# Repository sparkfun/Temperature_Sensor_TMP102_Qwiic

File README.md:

SparkFun Digital Temperature Sensor - TMP102 (Qwiic)
============================================

[  
*SparkFun Digital Temperature Sensor - TMP102 (Qwiic) (SEN-16304)*](https://www.sparkfun.com/products/16304)

Qwiic enabled breakout board for TMP102 digital temperature sensor [The datasheet can be found here.](https://www.sparkfun.com/datasheets/Sensors/Temperature/tmp102.pdf)

This board was created in Eagle v6.4.0. 

Repository Contents
-------------------

* **/Documentation** - Datasheet for the TMP102 (.pdf)
* **/Hardware** - All Eagle design files (.brd and .sch)
* **/Production** - Production panel files

Documentation
--------------
* **[Library](https://github.com/sparkfun/SparkFun_TMP102_Arduino_Library)** - Arduino library for the SparkFun Digital Temperature Sensor - TMP102 (Qwiic).
* **[Hookup Guide](https://learn.sparkfun.com/tutorials/sparkfun-qwiic-digital-temperature-sensor---tmp102-hookup-guide)** - Basic hookup guide for the SparkFun Digital Temperature Sensor - TMP102 (Qwiic).
  
License Information
-------------------
The hardware is released under [Creative Commons Share-alike 3.0](http://creativecommons.org/licenses/by-sa/3.0/).  
All other code is open source so please feel free to do anything you want with it; you buy me a beer if you use this and we meet someday ([Beerware license](http://en.wikipedia.org/wiki/Beerware)).

Design by Kade Alexander Jensen

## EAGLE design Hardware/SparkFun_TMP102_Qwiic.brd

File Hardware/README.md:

SparkFun Temperature Sensor TMP102 (Qwiic) Design Files
=====================================

The .sch and .brd files hare are Eagle CAD schematic and PCB design files from SparkFun Electronics.
A freeware version of Eagle can be found [here](http://www.cadsoftusa.com/download-eagle/freeware/).

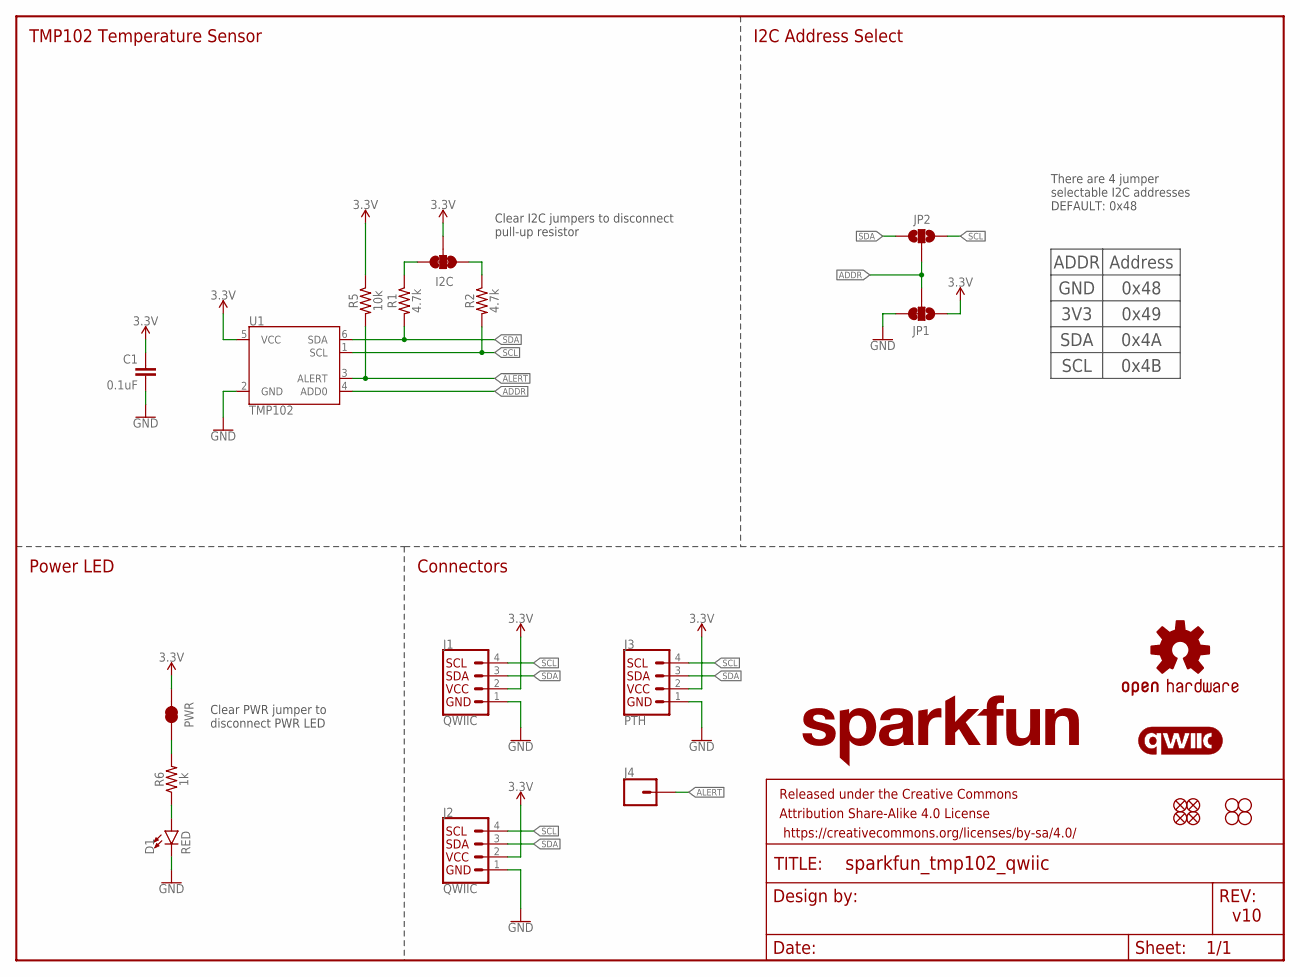
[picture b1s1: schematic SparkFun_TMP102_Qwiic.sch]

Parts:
C1: 0.1uF; 0603
D1: RED; LED-0603
FD1, FD2, FD3, FD4: FIDUCIALUFIDUCIAL; FIDUCIAL-MICRO
FRAME1: FRAME-LETTER; CREATIVE_COMMONS
H1, H2, H3, H4: STAND-OFF
J1, J2: QWIIC; JST04_1MM_RA
J3: PTH; 1X04_NO_SILK
J4: CONN_01PTH_NO_SILK_YES_STOP; 1X01_NO_SILK
JP1: JUMPER-SMT_3_1-NC_TRACE_NO-SILK; SMT-JUMPER_3_1-NC_TRACE_NO-SILK
JP2: JUMPER-SMT_3_NO_NO-SILK; SMT-JUMPER_3_NO_NO-SILK
JP3: I2C; SMT-JUMPER_3_2-NC_TRACE_SILK
JP4: PWR; SMT-JUMPER_2_NC_TRACE_SILK
LOGO1: SFE_LOGO_NAME.1_INCH; SFE_LOGO_NAME_.1
LOGO2: QWIIC_LOGO_5MM; QWIIC_5MM
LOGO3: OSHW-LOGOS; OSHW-LOGO-S
R1, R2: 4.7k; 0603
R5: 10k; 0603
R6: 1k; 0603
U1: TMP102; SOT563

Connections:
3.3V: C1.1, J1.2, J2.2, J3.2, JP1.1, JP3.2, JP4.2, R5.1, U1.5 (VCC)
!ALERT: J4.1, R5.2, U1.3 (ALERT)
ADDR: JP1.2, JP2.2, U1.4 (ADD0)
GND: C1.2, D1.C, J1.1, J2.1, J3.1, JP1.3, U1.2 (GND)
unnamed: JP3.3, R1.1
unnamed: JP3.1, R2.1
unnamed: D1.A, R6.1
unnamed: JP4.1, R6.2
SCL: J1.4, J2.4, J3.4, JP2.1, R2.2, U1.1 (SCL)
SDA: J1.3, J2.3, J3.3, JP2.3, R1.2, U1.6 (SDA)

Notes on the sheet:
v10
Address
0x48
0x49
0x4A
0x4B
GND
3V3
SDA
SCL
ADDR
I2C Address Select
TMP102 Temperature Sensor
Connectors
There are 4 jumper selectable I2C addresses DEFAULT: 0x48
Clear I2C jumpers to disconnect pull-up resistor
Clear PWR jumper to disconnect PWR LED
Power LED

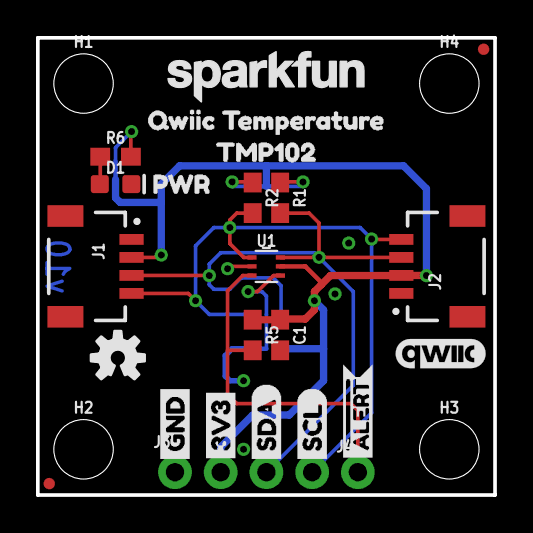
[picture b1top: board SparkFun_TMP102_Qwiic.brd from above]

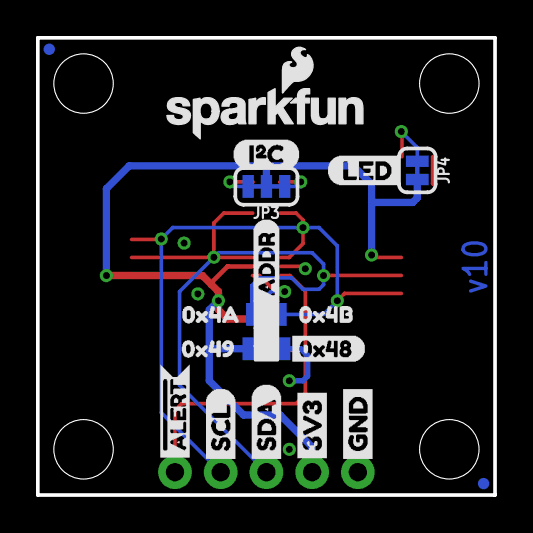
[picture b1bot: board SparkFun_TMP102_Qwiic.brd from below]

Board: 2 copper layers, 25.4 x 25.4 mm, 48 parts (19 on the bottom side), 10 nets.

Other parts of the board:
U$1, U$10: #ALERT8
U$2, U$9: SCL7
U$3, U$8: SDA6
U$4, U$7: 3V35
U$5, U$6: GND4
U$11: ADDR0
U$12: 0X481
U$13: 0X494
U$14: 0X4A2
U$15: 0X4B3
U$16: I#C0
U$17: LED0
U$18: QWIIC_TEMPERATURE0
U$19: TMP1022
U$20: PWR1
U$21: SFE_LOGO_NAME_FLAME_.1

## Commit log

2020-02-03 intial commit
2020-02-04 v10 design review changes
    - Added designer name to schematic
    - Mitered I2C pull-up trances going to via

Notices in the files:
parts and their libraries:
SparkFun-Capacitors: Licensing: Creative Commons ShareAlike 4.0 International - https://creativecommons.org/licenses/by-sa/4.0
SparkFun-Aesthetics: Released under the Creative Commons Attribution Share-Alike 4.0 License
SparkFun-Aesthetics: https://creativecommons.org/licenses/by-sa/4.0
